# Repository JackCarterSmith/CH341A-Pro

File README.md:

# CH341A-Pro2

Originally by Upcycle-Electronics, thanks to him! (https://github.com/Upcycle-Electronics/CH341A-Pro)

I've added a voltage selection jumper, swap the memory orientation (to follow the last software revision) and removed the "useless" serial I/O.
For now, this version haven't been tested... Please be advice!

Schematic:
https://github.com/JackCarterSmith/CH341A-Pro/blob/master/ch341Apro_schematicV02a.pdf

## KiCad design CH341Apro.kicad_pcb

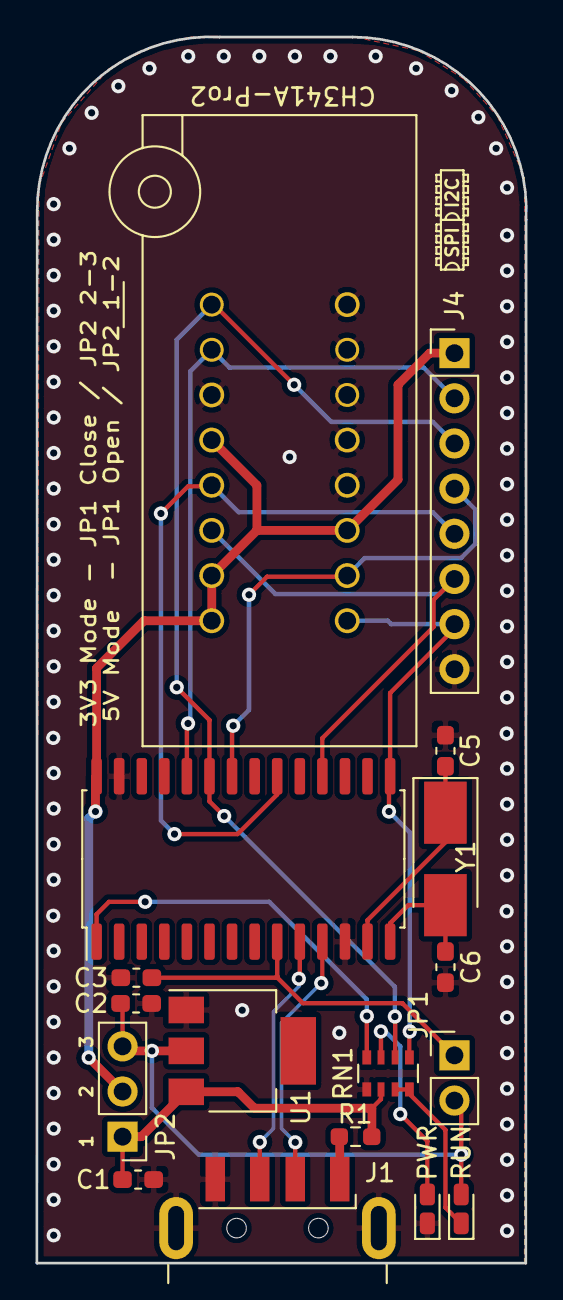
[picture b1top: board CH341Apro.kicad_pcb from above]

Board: 2 copper layers, 27.5 x 69.0 mm, 17 parts (0 on the bottom side), 19 nets.

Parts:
C1, C2: 104; C_0603_1608Metric_Pad1.05x0.95mm_HandSolder
C3: 472; C_0603_1608Metric_Pad1.05x0.95mm_HandSolder
C5, C6: 20p; C_0603_1608Metric_Pad1.05x0.95mm_HandSolder
J1: USB_A; USB_A_CNCTech_1001-011-01101_Horizontal
J3: ZIF-16; DIP_Socket-16_W4.3_W5.08_W7.62_W10.16_W10.9_3M_216-3340-00-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
J4: PinHeader_1x08_P2.54mm_Vertical
JP1: PinHeader_1x02_P2.54mm_Vertical
JP2: V_SEL; PinHeader_1x03_P2.54mm_Vertical
PWR: PWR; LED_0603_1608Metric_Castellated
R1: 0R; R_0603_1608Metric_Pad0.98x0.95mm_HandSolder
RN1: 222; R_Array_Convex_4x0603
RUN: RUN; LED_0603_1608Metric_Castellated
U1: AMS1117-3.3; SOT-223-3_TabPin2
U2: CH341a; SOIC-28W_7.5x17.9mm_P1.27mm
Y1: 12M; Crystal_SMD_5032-2Pin_5.0x3.2mm_HandSoldering

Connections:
/3V3: C2.1, JP1.2, JP2.3, RUN.2, U1.2
/5V: C1.1, JP2.1, R1.1, RN1.6, U1.3
/CLK: J3.6, J4.6, U2.18
/CS: J3.9, J4.7, RN1.1, U2.15
/MISO: J3.10, J4.4, U2.22
/MOSI: J3.5, J4.5, U2.20
/SCL: J3.2, J4.2, U2.24
/SDA: J3.1, J4.3, RN1.2, U2.23
/USB_N: J1.2, U2.11
/USB_P: J1.3, U2.10
/VCC: J3.4, J3.7, J3.8, J3.11, J4.1, JP2.2, U2.28
Earth: C1.2, C2.2, C3.1, C5.2, C6.2, J1.4, J1.5, J3.3, J3.12, J3.13, J3.14, J3.15, J3.16, J4.8, PWR.1, RN1.5, U1.1, U2.12, U2.27
unnamed: C3.2, JP1.1, U2.9
unnamed: C5.1, U2.13, Y1.1
unnamed: C6.1, U2.14, Y1.2
unnamed: PWR.2, RN1.3
unnamed: RN1.7, RN1.8, RUN.1
unnamed: J1.1, R1.2
unnamed: RN1.4, U2.1

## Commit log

2021-02-26 Updated schematic and PCB
    Read the README file for details
2021-02-26 Add .gitignore
2021-02-26 Add JLCPCB assembly infos
2021-03-12 Major ergo change
    Updated components footprints for hand soldering.
    Change VCC routing.
    Add JP1/2 for selecting operating voltage.
2021-03-15 Changed drawing and placement
